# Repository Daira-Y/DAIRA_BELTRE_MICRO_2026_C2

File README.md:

# DAIRA_BELTRE_MICRO_2026_C2
Repositorio Microcontroladores

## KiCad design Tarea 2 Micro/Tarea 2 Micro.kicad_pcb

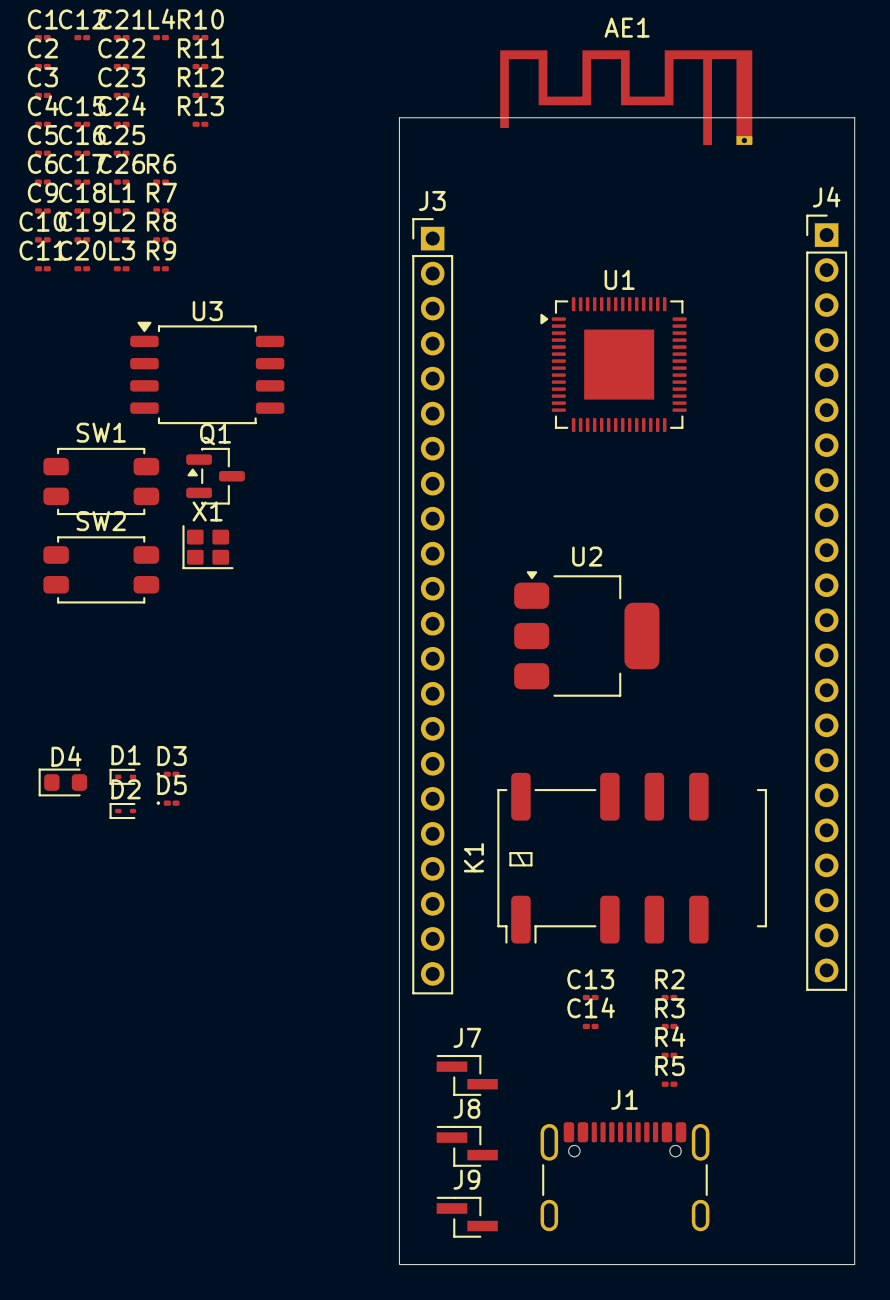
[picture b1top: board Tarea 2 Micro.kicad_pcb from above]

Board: 2 copper layers, 26.0 x 65.5 mm, 60 parts (0 on the bottom side), 73 nets, no tracks yet.

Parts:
AE1: Antenna_Chip; Texas_SWRA117D_2.4GHz_Left
C1, C3: 10uF; C_01005_0402Metric
C2, C4: 0.1uF; C_01005_0402Metric
C5, C6, C9, C10, C11, C12, C13, C14, C15, C16, C17, C18, C19, C20, C21, C22, C23, C24, C25, C26: C_01005_0402Metric
D1, D2: ESD9B3.3ST5G; D_SOD-923
D3, D5: LED; LED_01005_0402Metric
D4: D; D_0603_1608Metric
J1: USB_C_Receptacle_USB2.0_14P; USB_C_Receptacle_GCT_USB4105-xx-A_16P_TopMnt_Horizontal
J3, J4: Conn_01x22_Socket; PinHeader_1x22_P2.00mm_Vertical
J7, J8, J9: Conn_01x02_Pin; PinHeader_1x02_P1.00mm_Vertical_SMD_Pin1Left
K1: EE2-3NKX; Relay_DPDT_Kemet_EE2_NUX_NKX
L1, L2, L3, L4: L; L_01005_0402Metric
Q1: MMBT3904; SOT-23
R2, R3, R4, R5, R6, R7, R8, R9, R10, R11, R12, R13: R; R_01005_0402Metric
SW1, SW2: SW_Push; SW_SPST_EVQP2_MiddlePushTravel_H2.5mm
U1: ESP32-S3; QFN-56-1EP_7x7mm_P0.4mm_EP4x4mm
U2: AMS1117-3.3; SOT-223-3_TabPin2
U3: W25Q16JVSS; SOIC-8_5.3x5.3mm_P1.27mm
X1: SMD7050-4; Crystal_SMD_SeikoEpson_FA128-4Pin_2.0x1.6mm

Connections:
+3.3V: C3.1, C4.1, C15.1, C16.1, C17.1, C18.1, C20.2, C21.2, C22.2, C23.2, C24.2, C25.2, C26.1, D2.2 (A2), D3.2 (A), J3.1, J3.2, L4.1, R13.1, SW2.1, U1.20 (VDD3P3_RTC), U1.29 (VDD_SPI), U1.46 (VDD3P3_CPU), U1.55 (VDDA), U1.56 (VDDA), U2.2 (VO)
+5V: C1.1, C2.1, D4.1 (K), J1.A4 (VBUS), J1.A9 (VBUS), J1.B4 (VBUS), J1.B9 (VBUS), J3.21, K1.12, Q1.3 (C), U2.3 (VI)
CHIP_PU: R13.2, SW1.1, U1.4 (CHIP_PU)
GND: AE1.2 (PCB_Trace), C1.2, C2.2, C3.2, C4.2, C5.2, C6.2, C9.2, C10.2, C11.2, C12.2, C13.2, C14.1, C15.2, C16.2, C17.2, C18.2, C19.2, C20.1, C21.1, C22.1, C23.1, C24.1, C25.1, C26.2, D1.1 (A1), D2.1 (A1), D3.1 (K), D4.2 (A), D5.1 (K), J1.A1 (GND), J1.A12 (GND), J1.B1 (GND), J1.B12 (GND), J1.SH (SHIELD), J3.22, J4.1, J4.21, J4.22, K1.1, R4.2, R5.2, SW1.2, U1.57 (GND), U2.1 (GND), U3.4 (GND), X1.2, X1.4
GPIO0: J4.14, U1.5 (GPIO0)
GPIO1: J4.4, U1.6 (GPIO1)
GPIO2: J4.5, U1.7 (GPIO2)
GPIO3: J3.13, U1.8 (GPIO3)
GPIO4: J3.4, U1.9 (GPIO4)
GPIO5: J3.5, U1.10 (GPIO5)
GPIO6: J3.6, U1.11 (GPIO6)
GPIO7: J3.7, U1.12 (GPIO7)
GPIO8: J3.12, U1.13 (GPIO8)
GPIO9: J3.15, U1.14 (GPIO9)
GPIO10: J3.16, U1.15 (GPIO10)
GPIO11: J3.17, U1.16 (GPIO11)
GPIO12: J3.18, U1.17 (GPIO12)
GPIO13: J3.19, U1.18 (GPIO13)
GPIO14: J3.20, U1.19 (GPIO14)
GPIO17: J3.10, U1.23 (GPIO17)
GPIO18: J3.11, U1.24 (GPIO18)
GPIO21: J4.18, U1.27 (GPIO21)
GPIO33: R12.2, U1.38 (GPIO33)
GPIO34: SW2.2, U1.39 (GPIO34)
GPIO35: J4.13, U1.40 (GPIO35)
GPIO36: J4.12, U1.41 (GPIO36)
GPIO37: J4.11, U1.42 (GPIO37)
GPIO38: J4.10, U1.43 (GPIO38)
GPIO39: J4.9, U1.44 (MTCK)
GPIO40: J4.8, U1.45 (MTDO)
GPIO41: J4.7, U1.47 (MTDI)
GPIO42: J4.6, U1.48 (MTMS)
GPIO45: J4.15, U1.51 (GPIO45)
GPIO46: J3.14, U1.52 (GPIO46)
GPIO47: J4.17, U1.37 (SPICLK_P)
GPIO48: J4.16, U1.36 (SPICLK_N)
unnamed: AE1.1 (FEED), C12.1, D1.2 (A2), L3.2
unnamed: C5.1, L1.2, X1.1
unnamed: C10.1, C11.1, L2.2, L3.1
unnamed: C13.1, J1.A6 (D+), J1.B6 (D+), R2.1
unnamed: C14.2, J1.A7 (D-), J1.B7 (D-), R3.1
unnamed: D5.2 (A), Q1.2 (E)
unnamed: J1.A5 (CC1), R5.1
unnamed: J1.B5 (CC2), R4.1
unnamed: J7.1, K1.4
unnamed: J7.2, K1.9
unnamed: J8.1, K1.10
unnamed: J8.2, K1.3
unnamed: J9.1, K1.8
unnamed: J9.2, K1.5
unnamed: Q1.1 (B), R12.1
unnamed: C9.1, L2.1, U1.1 (LNA_IN)
unnamed: R8.1, U1.33 (SPICLK)
unnamed: R6.1, U1.35 (SPID)
unnamed: R10.1, U1.30 (SPIHD)
unnamed: R7.1, U1.34 (SPIQ)
unnamed: R9.1, U1.31 (SPIWP)
unnamed: R11.1, U1.49 (U0TXD)
unnamed: C6.1, U1.53 (XTAL_N), X1.3
unnamed: L1.1, U1.54 (XTAL_P)
RX: J4.3, U1.50 (U0RXD)
SPICLK: R8.2, U3.6 (CLK)
SPICS0: U1.32 (SPICS0), U3.1 (~CS)
SPID: R6.2, U3.5 (DI/IO_{0})
SPIHD: R10.2, U3.7 (~HOLD/~RESET/IO_{3})
SPIQ: R7.2, U3.2 (DO/IO_{1})
SPIWP: R9.2, U3.3 (~WP/IO_{2})
TX: J4.2, R11.2
USB_D+: J4.19, R2.2, U1.26 (GPIO20/USB_D+)
USB_D-: J4.20, R3.2, U1.25 (GPIO19/USB_D-)
VDD3P3: C19.1, L4.2, U1.2 (VDD3P3), U1.3 (VDD3P3)
XTAL_32K_N: J3.9, U1.22 (XTAL_32K_N)
XTAL_32K_P: J3.8, U1.21 (XTAL_32K_P)

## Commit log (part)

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2026-06-12 Tareas 1 y 2
